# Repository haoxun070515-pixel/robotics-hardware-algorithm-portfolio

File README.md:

# robotics-hardware-algorithm-portfolio
Portfolio for Robotics: Algorithms (Localization &amp; 2-opt Planning) and Hardware Circuits (Push-Pull Power &amp; Signal Generator).

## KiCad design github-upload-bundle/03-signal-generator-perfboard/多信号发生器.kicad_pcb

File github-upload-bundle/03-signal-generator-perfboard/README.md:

# 🎯 四路高精度复合模拟信号发生器（35×38 洞洞板优化工程）

本工程复现全国大学生电子设计竞赛综合测评国赛真题。在极其严苛的物理约束下，完成信号链设计与高密度洞洞板物理拓扑重构。

## 极限约束与信号链
- **芯片约束**：仅限 1 片 LM324（四运放）+ 1 片 SN74LS00（与非门）
- **供电约束**：单一 +5V 单电源供电（自主设计 +2.5V 虚地偏置网络）
- **四路输出**：
  - Uo1 (J1)：19~21kHz 连续调频方波（Vpp ≥ 3.2V）
  - Uo2 (J2)：5%~15% 占空比连续可调窄脉冲
  - Uo3 (J3)：同频低失真正弦波（失真度 < 5%，Vpp ≥ 1V）
  - Uo4 (J4)：90° 正交余弦波（相位误差 ≤ 5°）

## 物理布局与攻坚（核心技术壁垒）
1. **网格干涉攻坚**：完美解决 3362P 品字形电位器与 5.08mm 螺钉接线端子与 2.54mm 网格的干涉；
2. **抗串扰物理分区**：以双 IC 为轴设计顺时针流向，彻底隔离高频脉冲与高阻微弱正弦滤波节点；
3. **飞线极致精简**：最大化采用焊锡就近搭桥，将整板跨区绝缘飞线**极限控制在约 20 条**；
4. **测试端子一字出线**：右侧边缘一字排列 J1~J4 端子，消除引线电感并极大提升示波器实调工效。

## 归档文件
- `多信号发生器_正面装配图.png`：35×38 坐标元件插装图
- `多信号发生器_背面接线图.png`：金色焊锡搭桥 + 20 根绝缘飞线走线图
- `多信号发生器_2019国赛.kicad_pcb` / `多信号发生器_2019国赛.kicad_pro`：KiCad/嘉立创工程

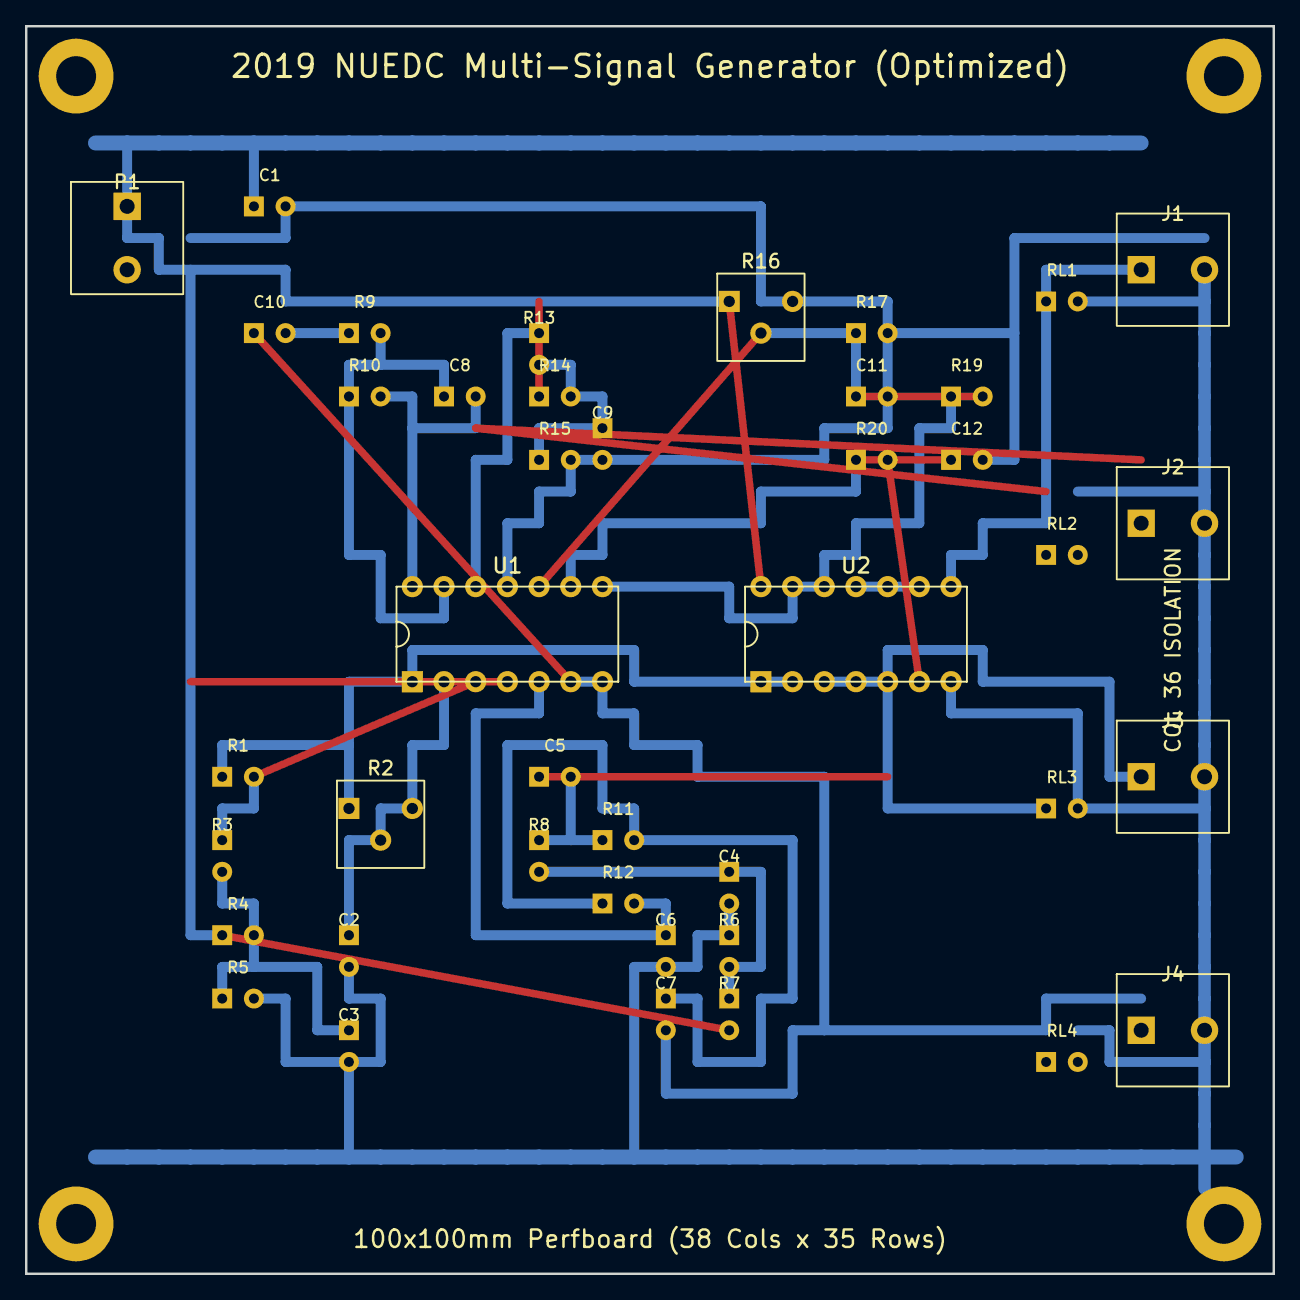
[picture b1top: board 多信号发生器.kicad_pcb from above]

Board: 2 copper layers, 100.0 x 100.0 mm, 42 parts (0 on the bottom side), 23 nets.

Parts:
C1, C3, C4, C5, C9, C11, C12: 104; C_Disc_D5.0mm_W2.5mm_P2.54mm
C2: 222; C_Disc_D5.0mm_W2.5mm_P2.54mm
C6, C7: 682; C_Disc_D5.0mm_W2.5mm_P2.54mm
C8: 102; C_Disc_D5.0mm_W2.5mm_P2.54mm
C10: 10uF; CP_Radial_D5.0mm_P2.50mm
J1: Uo1_SQUARE; TerminalBlock_bornier-2_P5.0mm
J2: Uo2_PULSE; TerminalBlock_bornier-2_P5.0mm
J3: Uo3_SINE; TerminalBlock_bornier-2_P5.0mm
J4: Uo4_COSINE; TerminalBlock_bornier-2_P5.0mm
P1: +5V/GND; TerminalBlock_bornier-2_P5.0mm
R1: 20k; R_Axial_DIN0207_L6.3mm_D2.5mm_P7.62mm_Horizontal
R2: 20k; Potentiometer_Bourns_3362P_Vertical
R3, R13: 10k; R_Axial_DIN0207_L6.3mm_D2.5mm_P7.62mm_Horizontal
R4, R5, R14, R15, R17: 1k; R_Axial_DIN0207_L6.3mm_D2.5mm_P7.62mm_Horizontal
R6, R7, R8, R10, R19: 100k; R_Axial_DIN0207_L6.3mm_D2.5mm_P7.62mm_Horizontal
R9: 9.1k; R_Axial_DIN0207_L6.3mm_D2.5mm_P7.62mm_Horizontal
R11, R12: 2k; R_Axial_DIN0207_L6.3mm_D2.5mm_P7.62mm_Horizontal
R16: 10k; Potentiometer_Bourns_3362P_Vertical
R20: 100R; R_Axial_DIN0207_L6.3mm_D2.5mm_P7.62mm_Horizontal
RL1, RL2, RL3, RL4: 1k; R_Axial_DIN0207_L6.3mm_D2.5mm_P7.62mm_Horizontal
U1: LM324N; DIP-14_W7.62mm
U2: SN74LS00N; DIP-14_W7.62mm

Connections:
COS_FB: C8.1, R9.2, R10.1, U1.13
COS_IN: C10.2, R9.1
COS_PLUS: R13.1, U1.12
GND: C1.2, C2.2, C3.2, C4.2, C6.2, C9.2, C11.2, C12.2, J1.2, J2.2, J3.2, J4.2, P1.2, R5.2, R6.1, R15.2, R17.2, RL1.2, RL2.2, RL3.2, RL4.2, U1.11, U2.7
INV_Uo1: R20.2, U2.6
LPF_N1: C5.2, R8.1, R11.1
LPF_N2: C7.1, R11.2, R12.1
LPF_OUT: C6.1, R12.2, U1.5
OSC_INV: C2.1, R2.2, R2.3, U1.2
OSC_OUT: R1.1, R2.1, U1.1, U2.1, U2.2
OSC_PLUS: R1.2, R3.1, U1.3
PULSE_IN: C12.1, R20.1, U1.9
PULSE_RAW: R19.1, U1.8, U2.12, U2.13
PULSE_REF: C11.1, R16.2, R16.3, R17.1, R19.2, U1.10
PULSE_SHAPE: U2.9, U2.10, U2.11
Uo1: C5.1, J1.1, RL1.1, U2.3, U2.4, U2.5
Uo2: J2.1, RL2.1, U2.8
Uo3: C7.2, C10.1, J3.1, RL3.1, U1.6, U1.7
Uo4: C8.2, J4.1, R10.2, RL4.1, U1.14
VCC: C1.1, P1.1, R4.1, R7.2, R14.1, R16.1, U1.4, U2.14
VREF_A: C3.1, R3.2, R4.2, R5.1
VREF_B: C4.1, R6.2, R7.1, R8.2
VREF_C: C9.1, R13.2, R14.2, R15.1
